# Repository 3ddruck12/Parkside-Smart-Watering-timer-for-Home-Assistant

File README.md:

Operate the Parkside Smart Watering Timer with ESP Home.
https://www.lidl.de/p/parkside-bewaesserungscomputer-pbb-a1-mit-bluetooth/p100348186

Dual H Bridge drv8833
https://spacehal.github.io/docs/motor/drv8833
https://www.ti.com/lit/ds/symlink/drv8833.pdf

AT42QT1012-TSHR Touch Sensor

ESP 8266 12E

Credits
https://forum.makerspace-gt.de/t/smarte-bewaesserung/745

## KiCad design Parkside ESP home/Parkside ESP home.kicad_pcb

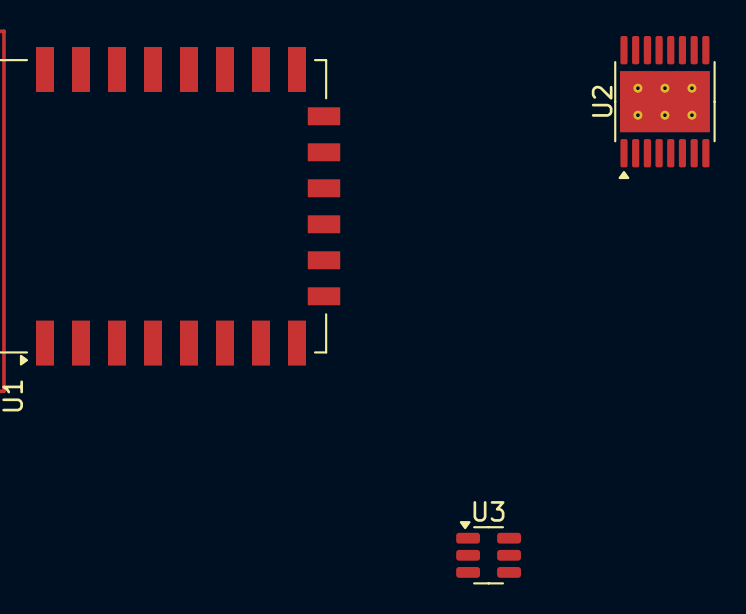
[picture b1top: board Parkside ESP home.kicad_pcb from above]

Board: 2 copper layers, 3 parts (0 on the bottom side), 5 nets, no tracks yet.

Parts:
U1: ESP-12E
U2: DRV8833PWP; HTSSOP-16-1EP_4.4x5mm_P0.65mm_EP3.4x5mm_Mask2.46x2.31mm_The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
U3: AT42QT1011-TSHR; SOT-23-6

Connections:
unnamed: U1.8 (VCC), U2.14 (VINT), U3.5 (VDD)
unnamed: U2.13 (GND), U2.17 (GND), U3.2 (VSS)
unnamed: U1.19 (GPIO4), U2.16 (AIN1)
unnamed: U1.20 (GPIO5), U2.15 (AIN2)
unnamed: U1.4 (GPIO16), U3.1 (OUT)
